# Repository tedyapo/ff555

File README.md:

# ff555
Fast 555-like timer circuit

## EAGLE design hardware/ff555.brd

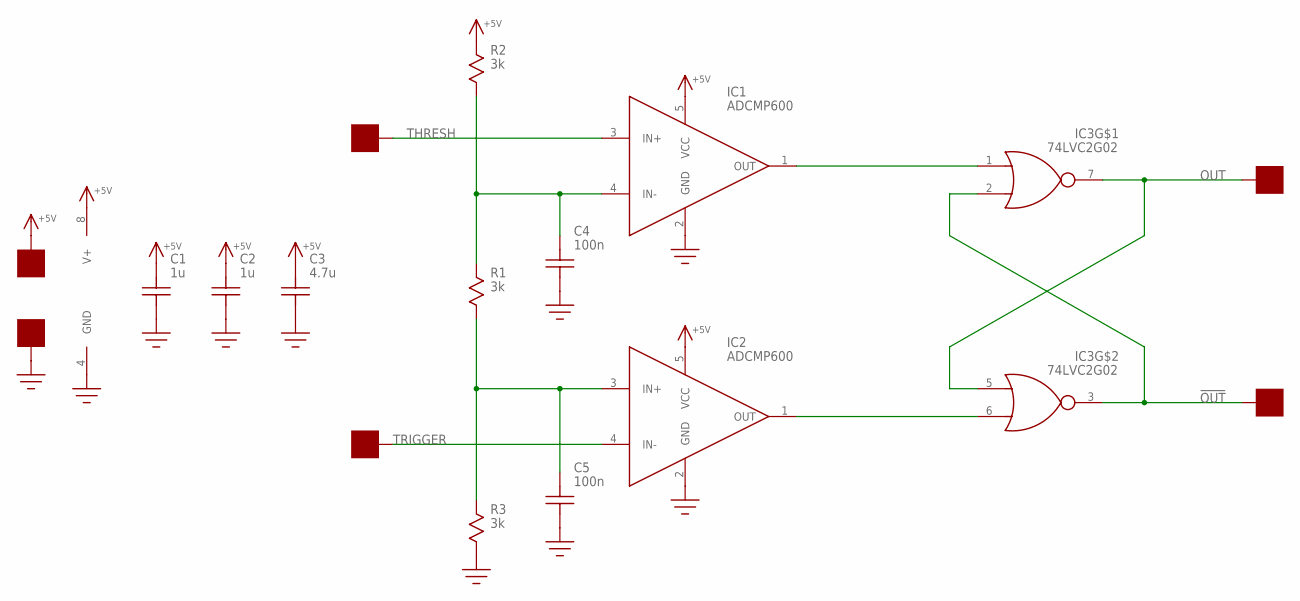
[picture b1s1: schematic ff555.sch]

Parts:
C1, C2: 1u; C0603
C3: 4.7u; 0805
C4, C5: 100n; C0603
IC1, IC2: ADCMP600; SOT23-5
IC3: 74LVC2G02; TSSOP8
R1: 3k; R1206
R2, R3: 3k; R0603
U$15, U$16, U$17, U$18, U$19, U$20: PAD100MIL; PAD_100MIL

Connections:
!OUT!: IC3.2 (B), IC3.3 (Y), U$20.P$1
+5V: C1.P$2, C2.P$2, C3.P$2, IC1.5 (VCC), IC2.5 (VCC), IC3.8 (V+), R2.P$1, U$15.P$1
GND: C1.P$1, C2.P$1, C3.P$1, C4.P$1, C5.P$1, IC1.2 (GND), IC2.2 (GND), IC3.4 (GND), R3.P$2, U$16.P$1
unnamed: C4.P$2, IC1.4 (IN-), R1.P$1, R2.P$2
unnamed: C5.P$2, IC2.3 (IN+), R1.P$2, R3.P$1
unnamed: IC1.1 (OUT), IC3.1 (A)
unnamed: IC2.1 (OUT), IC3.6 (B)
OUT: IC3.5 (A), IC3.7 (Y), U$19.P$1
THRESH: IC1.3 (IN+), U$17.P$1
TRIGGER: IC2.4 (IN-), U$18.P$1

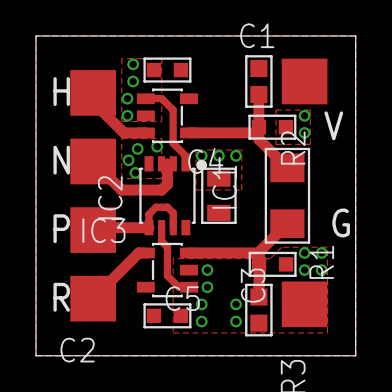
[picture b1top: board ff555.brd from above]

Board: 2 copper layers, 17.8 x 17.8 mm, 17 parts (0 on the bottom side), 10 nets.

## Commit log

2019-03-19 first checkin
2019-03-19 removed Eagle backup files
